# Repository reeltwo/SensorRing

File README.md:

# SensorRing
Absolute Position Rotary Encoder

Initial release of the PCBs. Sketch, patterns, and description to follow.

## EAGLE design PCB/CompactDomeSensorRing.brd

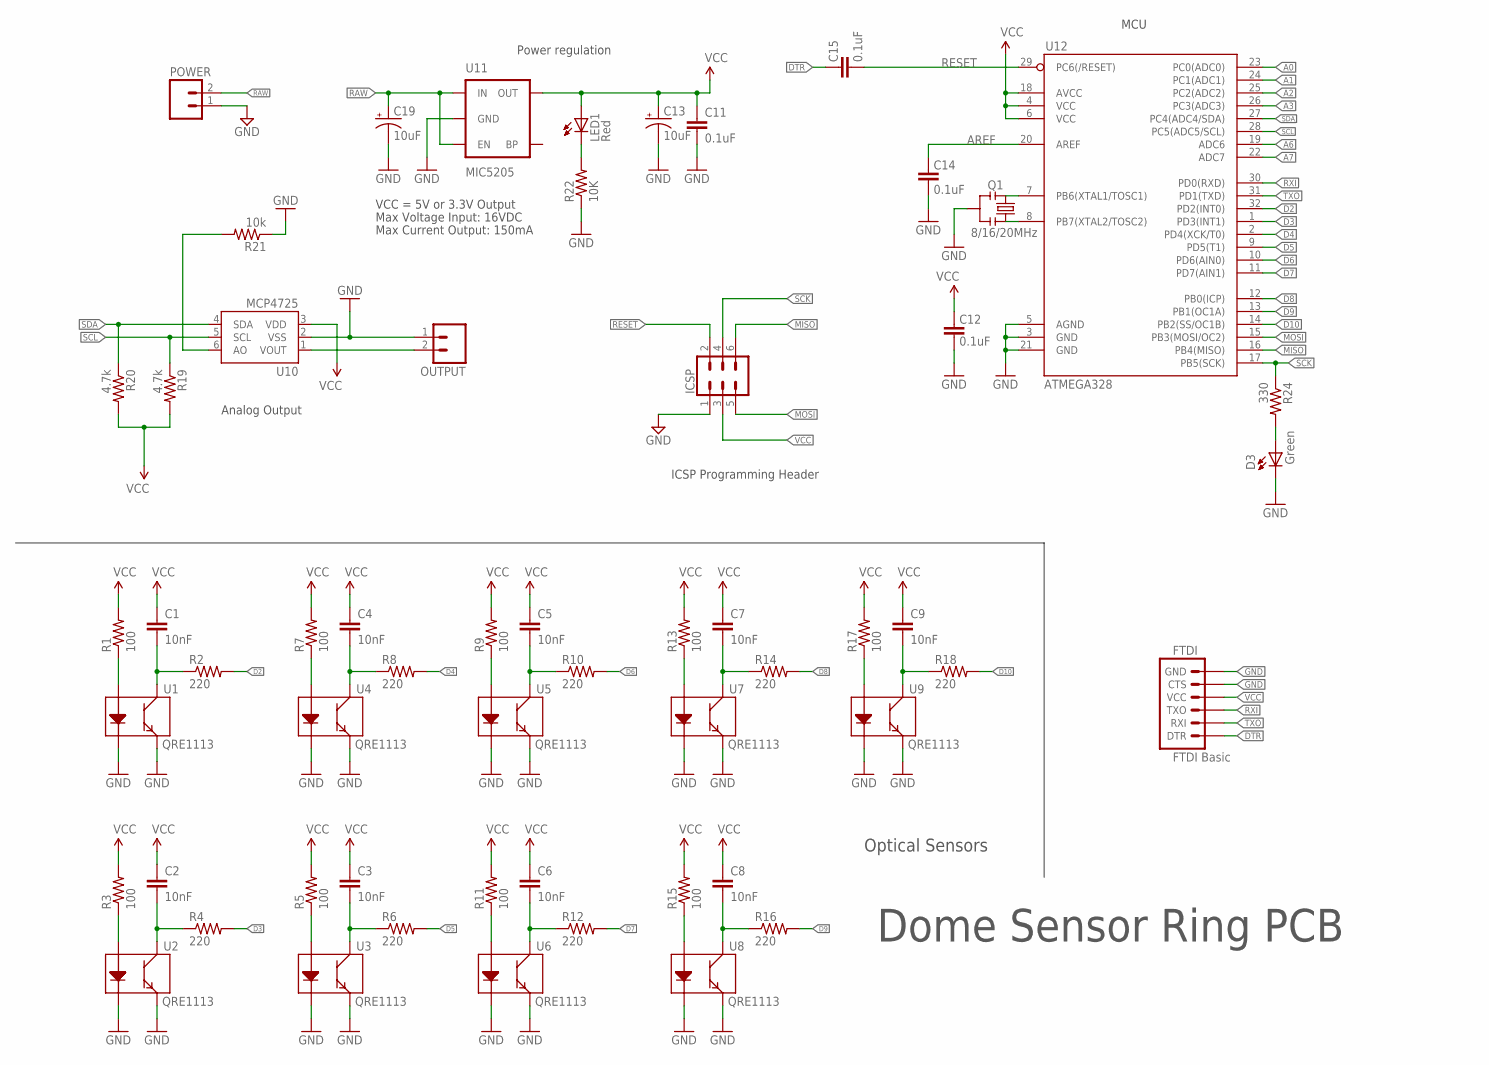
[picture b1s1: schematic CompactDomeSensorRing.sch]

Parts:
C1, C2, C3, C4, C5, C6, C7, C8, C9: 10nF; 0402-CAP
C11, C12, C14, C15: 0.1uF; 0603-CAP
C13, C19: 10uF; EIA3216
D3: Green; 0603-LED-ALT1
FTDI: FTDI Basic; 1X06
ICSP: CONN_03X2NO_SILK; 2X3-NS
LED1: Red; 0603-LED-ALT1
OUTPUT: M02PTH; 1X02
POWER: M02PTH; 1X02
Q1: 8/16/20MHz; RESONATOR-SMD-1:1
R1, R3, R5, R7, R9, R11, R13, R15, R17: 100; 0402-RES
R2, R4, R6, R8, R10, R12, R14, R16, R18: 220; 0402-RES
R19, R20: 4.7k; 0603-RES
R21: 10k; 0603-RES
R22: 10K; 0603-RES
R24: 330; 0603-RES
U1, U2, U3, U4, U5, U6, U7, U8, U9: QRE1113
U10: MCP4725; SOT23-6
U11: MIC5205; SOT23-5
U12: ATMEGA328; TQFP32-08

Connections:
A0: U12.23 (PC0(ADC0))
A1: U12.24 (PC1(ADC1))
A2: U12.25 (PC2(ADC2))
A3: U12.26 (PC3(ADC3))
A6: U12.19 (ADC6)
A7: U12.22 (ADC7)
AREF: C14.2, U12.20 (AREF)
D2: R2.2, U12.32 (PD2(INT0))
D3: R4.2, U12.1 (PD3(INT1))
D4: R8.2, U12.2 (PD4(XCK/T0))
D5: R6.2, U12.9 (PD5(T1))
D6: R10.2, U12.10 (PD6(AIN0))
D7: R12.2, U12.11 (PD7(AIN1))
D8: R14.2, U12.12 (PB0(ICP))
D9: R16.2, U12.13 (PB1(OC1A))
D10: R18.2, U12.14 (PB2(SS/OC1B))
DTR: C15.2, FTDI.1 (DTR)
GND: C11.2, C12.1, C13.C (-), C14.1, C19.C (-), D3.C, FTDI.5 (CTS), FTDI.6 (GND), ICSP.1, OUTPUT.1, POWER.1, Q1.2, R21.1, R22.1, U1.2 (K), U1.4 (E), U2.2 (K), U2.4 (E), U3.2 (K), U3.4 (E), U4.2 (K), U4.4 (E), U5.2 (K), U5.4 (E), U6.2 (K), U6.4 (E), U7.2 (K), U7.4 (E), U8.2 (K), U8.4 (E), U9.2 (K), U9.4 (E), U10.2 (VSS), U11.2 (GND), U12.3 (GND), U12.5 (AGND), U12.21 (GND)
MISO: ICSP.6, U12.16 (PB4(MISO))
MOSI: ICSP.5, U12.15 (PB3(MOSI/OC2))
unnamed: R1.1, U1.1 (A)
unnamed: R3.1, U2.1 (A)
unnamed: R5.1, U3.1 (A)
unnamed: R7.1, U4.1 (A)
unnamed: R9.1, U5.1 (A)
unnamed: R11.1, U6.1 (A)
unnamed: R13.1, U7.1 (A)
unnamed: R15.1, U8.1 (A)
unnamed: R17.1, U9.1 (A)
unnamed: R21.2, U10.6 (AO)
unnamed: D3.A, R24.2
unnamed: Q1.3, U12.8 (PB7(XTAL2/TOSC2))
unnamed: Q1.1, U12.7 (PB6(XTAL1/TOSC1))
unnamed: LED1.C, R22.2
OUT1: C1.2, R2.1, U1.3 (C)
OUT2: C2.2, R4.1, U2.3 (C)
OUT3: C3.2, R6.1, U3.3 (C)
OUT4: C4.2, R8.1, U4.3 (C)
OUT5: C5.2, R10.1, U5.3 (C)
OUT6: C6.2, R12.1, U6.3 (C)
OUT7: C7.2, R14.1, U7.3 (C)
OUT8: C8.2, R16.1, U8.3 (C)
OUT9: C9.2, R18.1, U9.3 (C)
RAW: C19.A (+), POWER.2, U11.1 (IN), U11.3 (EN)
RESET: C15.1, ICSP.2, U12.29 (PC6(/RESET))
RXI: FTDI.3 (TXO), U12.30 (PD0(RXD))
SCK: ICSP.4, R24.1, U12.17 (PB5(SCK))
SCL: R19.1, U10.5 (SCL), U12.28 (PC5(ADC5/SCL))
SDA: R20.1, U10.4 (SDA), U12.27 (PC4(ADC4/SDA))
TXO: FTDI.2 (RXI), U12.31 (PD1(TXD))
VCC: C1.1, C2.1, C3.1, C4.1, C5.1, C6.1, C7.1, C8.1, C9.1, C11.1, C12.2, C13.A (+), FTDI.4 (VCC), ICSP.3, LED1.A, R1.2, R3.2, R5.2, R7.2, R9.2, R11.2, R13.2, R15.2, R17.2, R19.2, R20.2, U10.3 (VDD), U11.5 (OUT), U12.4 (VCC), U12.6 (VCC), U12.18 (AVCC)
VOUT: OUTPUT.2, U10.1 (VOUT)

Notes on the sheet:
Max Voltage Input: 16VDC
Max Current Output: 150mA
VCC = 5V or 3.3V Output
Analog Output
ICSP Programming Header
Power regulation
MCU
Dome Sensor Ring PCB
Optical Sensors

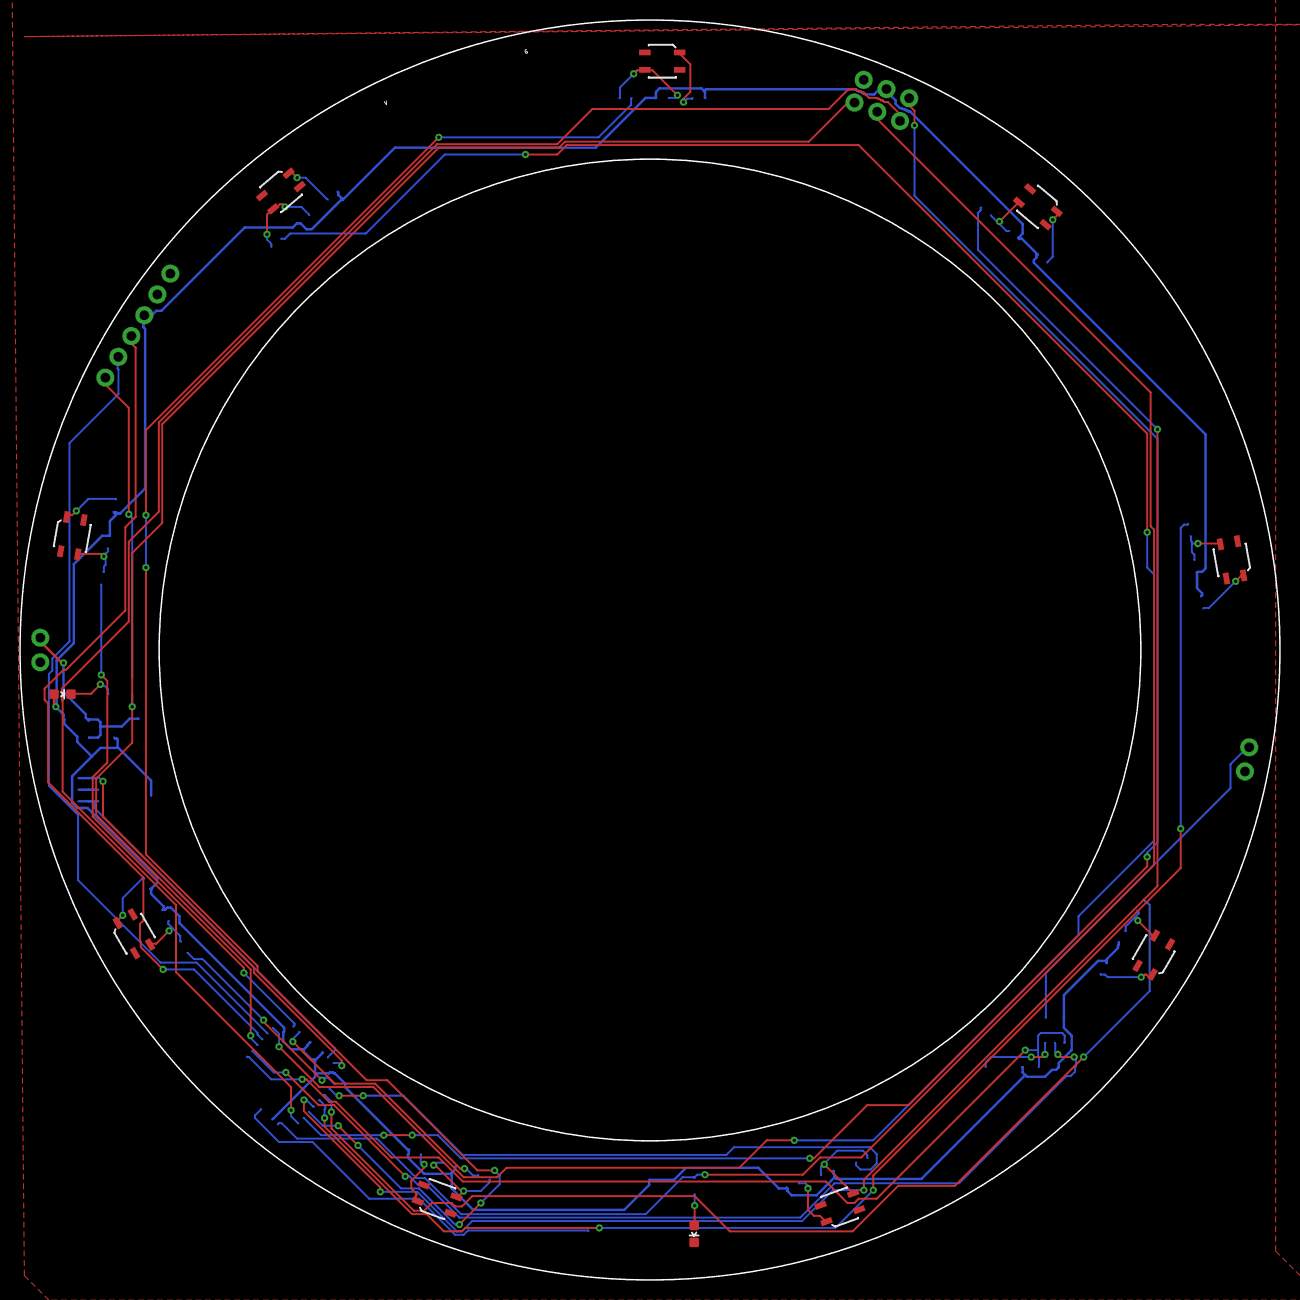
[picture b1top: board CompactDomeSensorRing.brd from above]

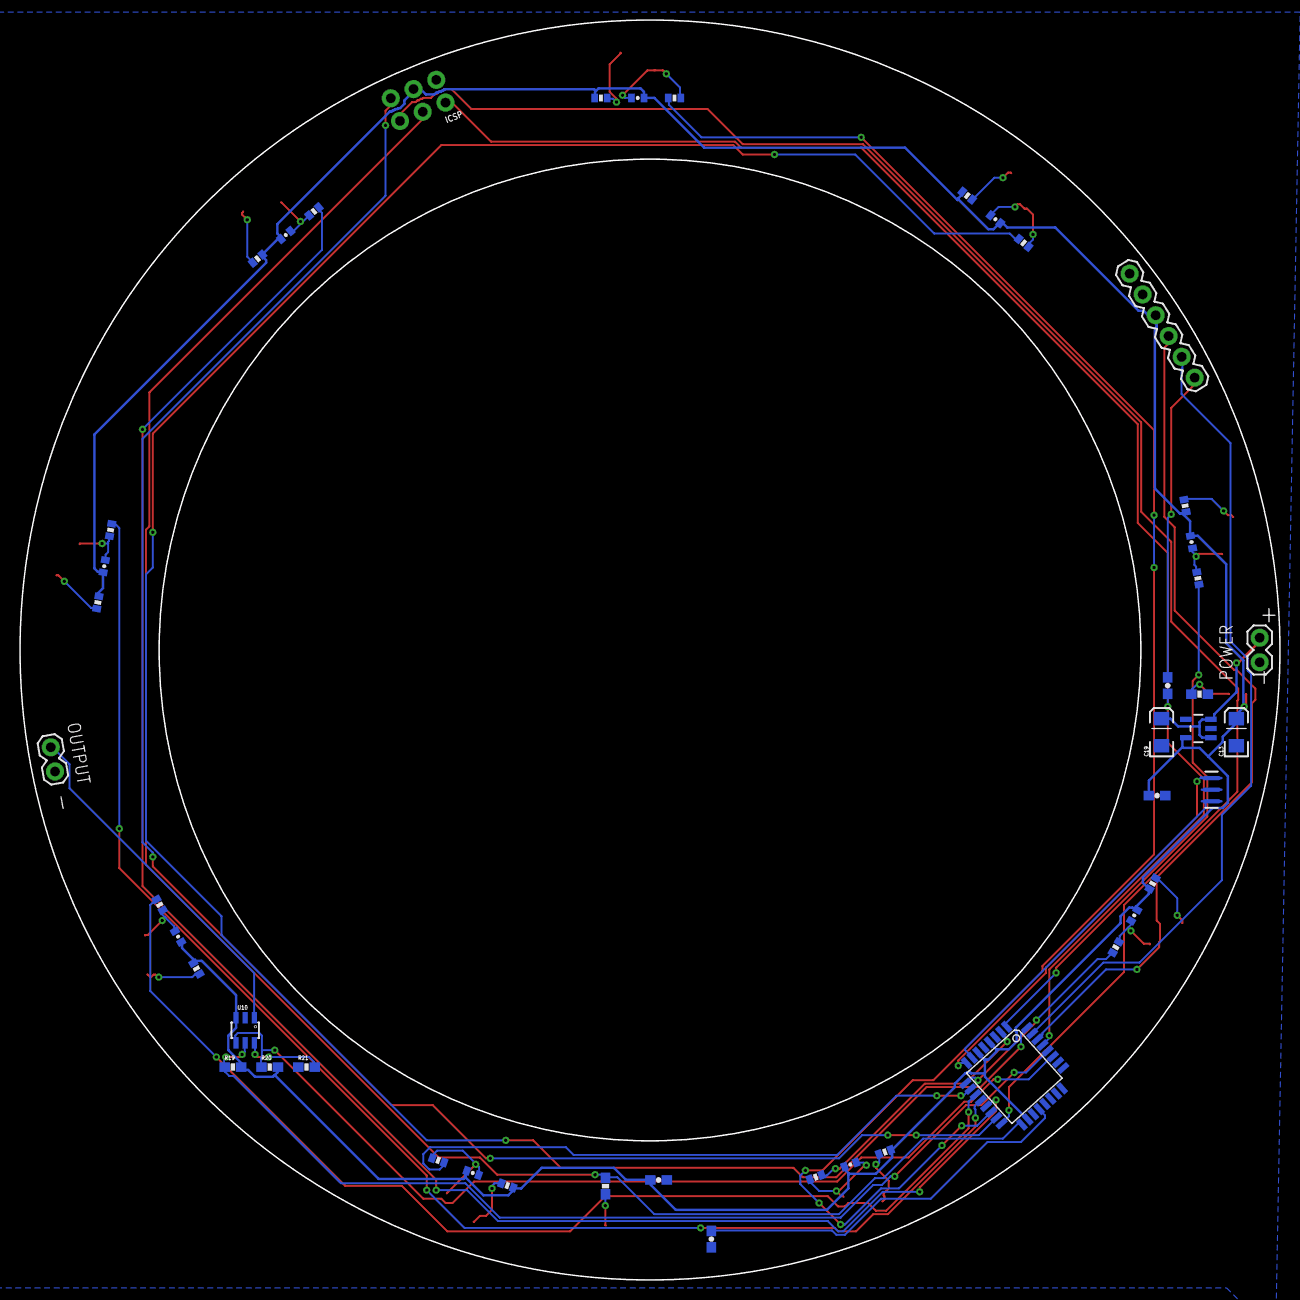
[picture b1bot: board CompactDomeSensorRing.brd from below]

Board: 2 copper layers, 130.4 x 130.4 mm, 57 parts (46 on the bottom side), 46 nets.

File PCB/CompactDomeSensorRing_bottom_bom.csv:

Comment,Designator,Footprint,LCSC Part #
0.1uF,C11 C12 C14 C15,0603-CAP,
4.7k,R19 R20,0603-RES,
8/16/20MHz,Q1,RESONATOR-SMD-1:1,
10K,R22,0603-RES,
10k,R21,0603-RES,
10nF,C1 C2 C3 C4 C5 C6 C7 C8 C9,0402-CAP,
10uF,C13 C19,EIA3216,
100,R1 R3 R5 R7 R9 R11 R13 R15 R17,0402-RES,
220,R2 R4 R6 R8 R10 R12 R14 R16 R18,0402-RES,
330,R24,0603-RES,
ATMEGA328,U12,TQFP32-08,
MCP4725,U10,SOT23-6,
MIC5205,U11,SOT23-5,

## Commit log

2022-01-07 Initial release
2022-01-07 Updated initial readme

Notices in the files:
parts and their libraries:
SparkFun-AnalogIC: Licensing:Creative Commons ShareAlike 4.0 International - https://creativecommons.org/licenses/by-sa/4.0
